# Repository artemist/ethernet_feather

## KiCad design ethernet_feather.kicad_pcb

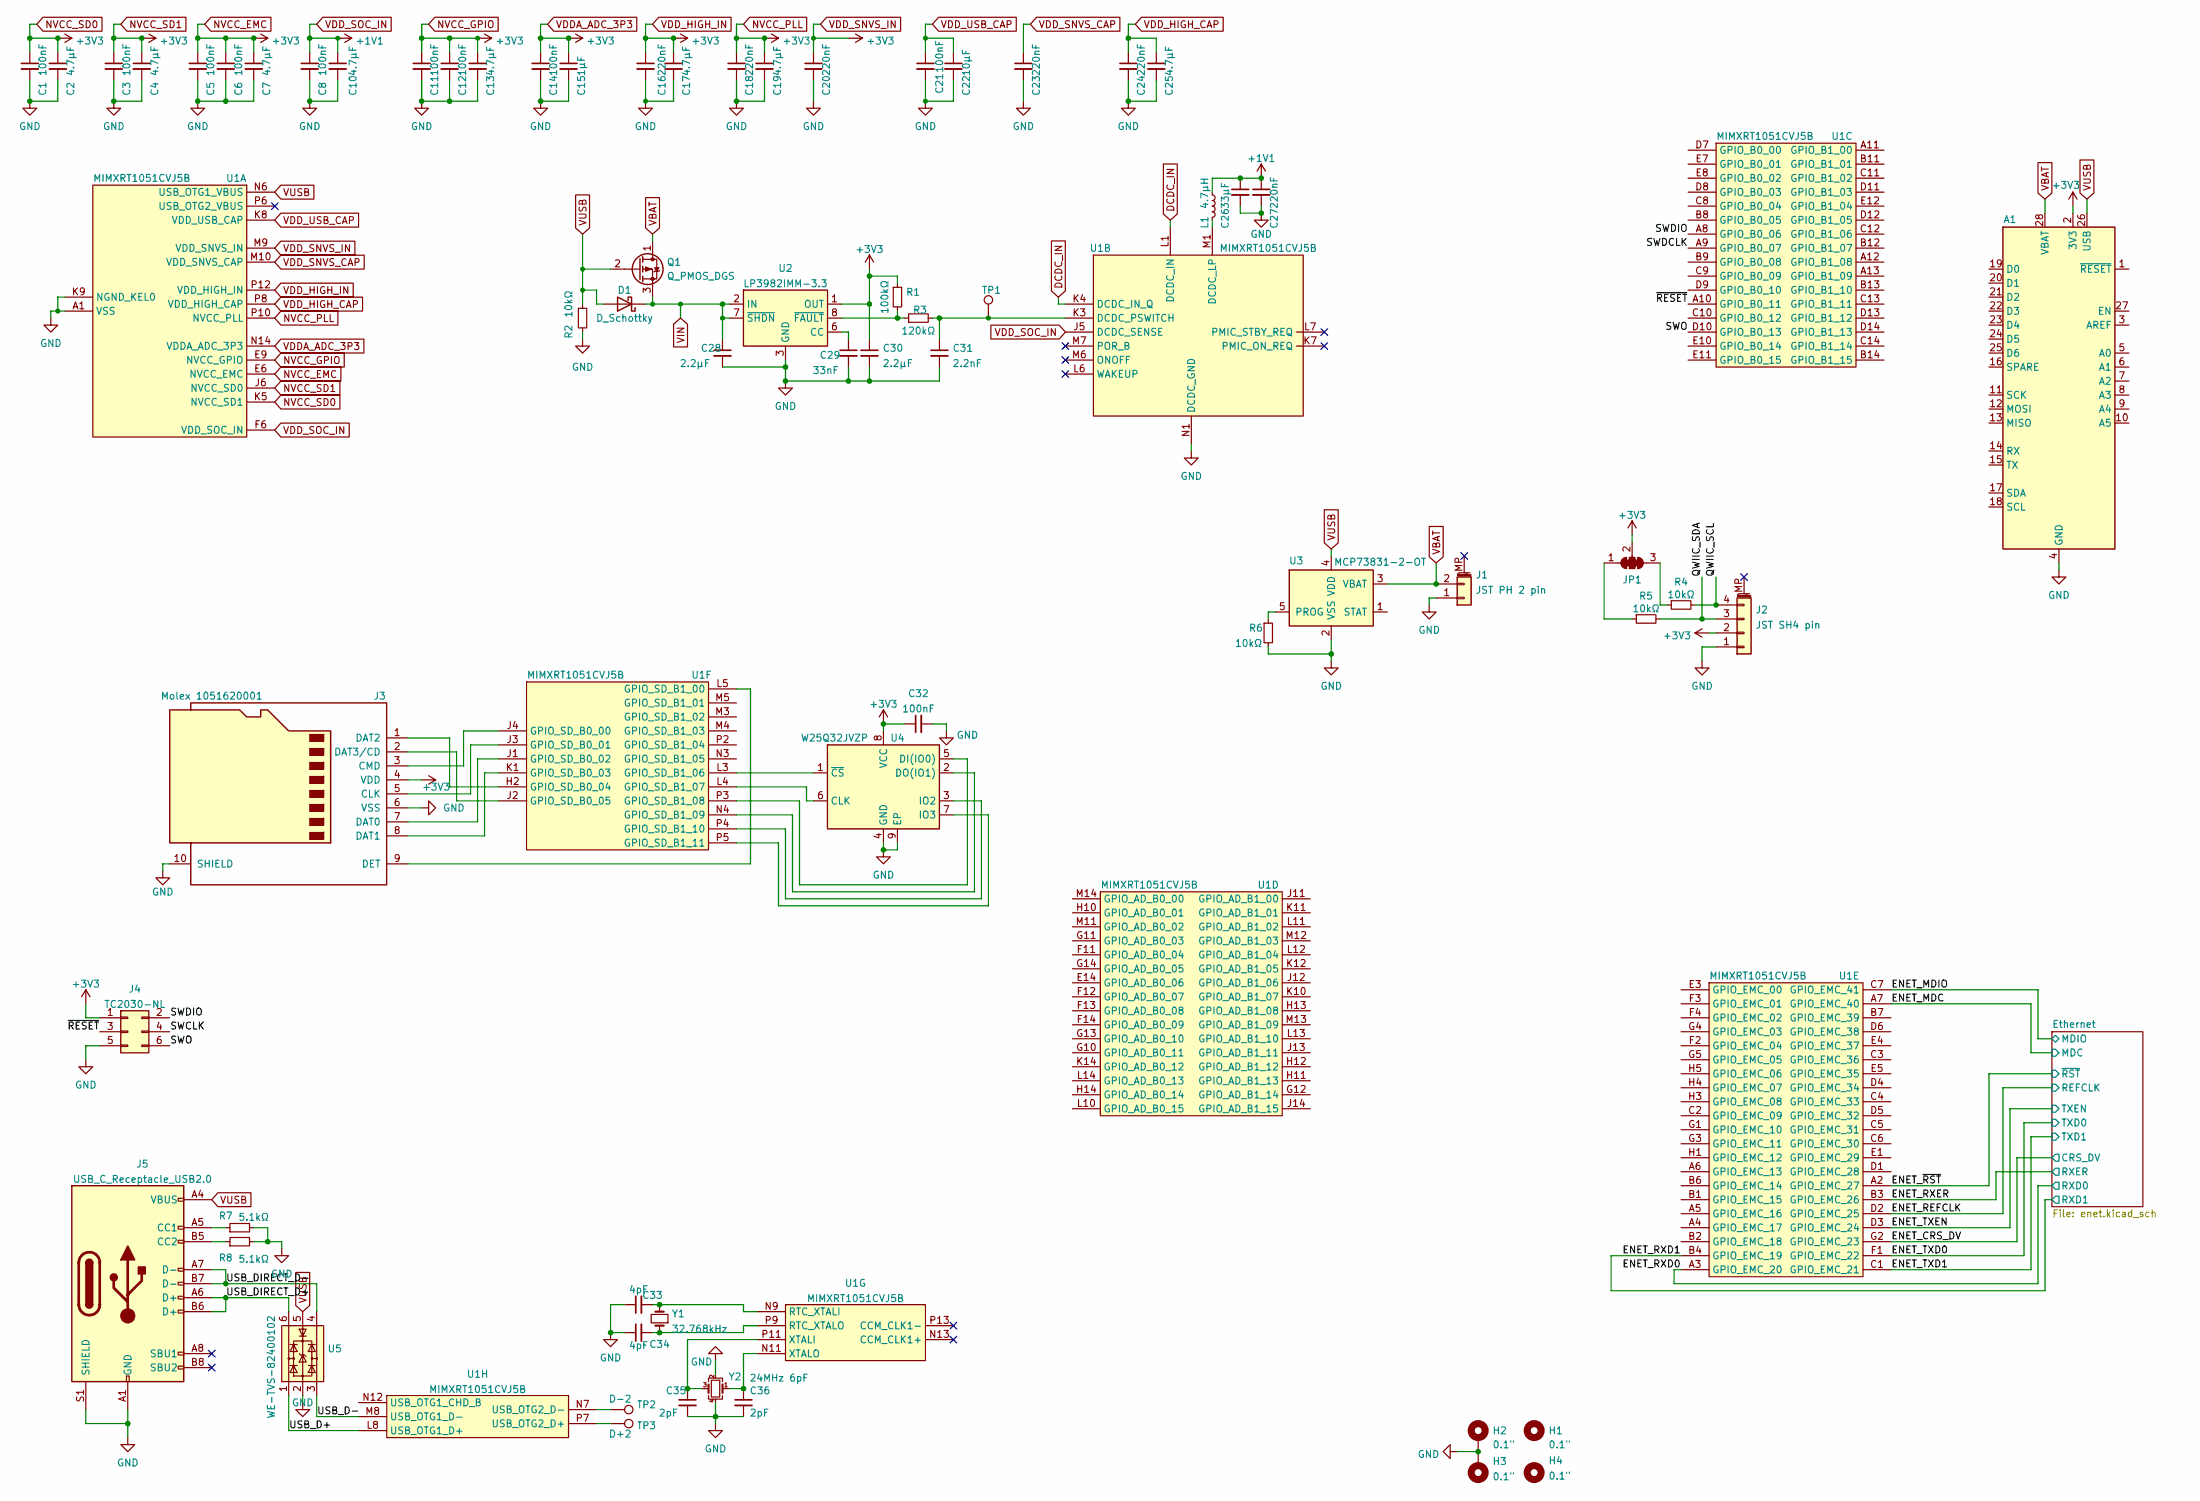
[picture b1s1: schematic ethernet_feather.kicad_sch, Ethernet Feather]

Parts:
A1: Adafruit_Feather_Generic; Adafruit_Feather
C1, C3, C5, C6, C8, C11, C12, C14, C21, C32: 100nF; C_0402_1005Metric
C2, C4, C7, C10, C13, C17, C19, C25: 4.7µF; C_0402_1005Metric
C15: 1µF; C_0402_1005Metric
C16, C18, C20, C23, C24, C27: 220nF; C_0402_1005Metric
C22: 10µF; C_0402_1005Metric
C26: 33µF; C_0402_1005Metric
C28, C30: 2.2µF; C_0402_1005Metric
C29: 33nF; C_0402_1005Metric
C31: 2.2nF; C_0402_1005Metric
C33, C34: 4pF; C_0402_1005Metric
C35, C36: 2pF; C_0402_1005Metric
D1: D_Schottky; D_SOD-323
H1, H4: 0.1"; MountingHole_2.5mm_Small
H2, H3: 0.1"; MountingHole_2.5mm_Pad_Small
J1: JST PH 2 pin; JST_PH_S2B-PH-SM4-TB_1x02-1MP_P2.00mm_Horizontal
J2: JST SH4 pin; JST_SH_SM04B-SRSS-TB_1x04-1MP_P1.00mm_Horizontal
J3: Molex 1051620001; microSD_HC_Molex_1051620001
J4: TC2030-NL; Tag-Connect_TC2030-IDC-NL_2x03_P1.27mm_Vertical
J5: USB_C_Receptacle_USB2.0; USB_C_Receptacle_HRO_TYPE-C-31-M-12
JP1: SolderJumper_3_Bridged123; SolderJumper-3_P1.3mm_Bridged123_RoundedPad1.0x1.5mm
L1: 4.7µH; L_0603_1608Metric
Q1: Q_PMOS_DGS; SOT-23
R1: 100kΩ; R_0402_1005Metric
R2, R4, R5, R6: 10kΩ; R_0402_1005Metric
R3: 120kΩ; R_0402_1005Metric
R7, R8: 5.1kΩ; R_0402_1005Metric
TP1: TestPoint; TestPoint_Pad_D1.0mm
TP2: D-2; TestPoint_Pad_D1.0mm
TP3: D+2; TestPoint_Pad_D1.0mm
U1: MIMXRT1051CVJ5B; LFBGA-196_12x12mm_Layout14x14_P0.8mm
U2: LP3982IMM-3.3; VSSOP-8_3.0x3.0mm_P0.65mm
U3: MCP73831-2-OT; SOT-23-5
U4: W25Q32JVZP; WSON-8-1EP_6x5mm_P1.27mm_EP3.4x4.3mm
U5: WE-TVS-82400102; SOT-23-6
Y1: 32.768kHz; Crystal_SMD_3215-2Pin_3.2x1.5mm
Y2: 24MHz 6pF; Crystal_SMD_2016-4Pin_2.0x1.6mm; Part Number XRCGB24M000F0L00R0

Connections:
/ENET_CRS_DV: U1.G2 (GPIO_EMC_23); also elsewhere on the board
/ENET_MDC: U1.A7 (GPIO_EMC_40); also elsewhere on the board
/ENET_MDIO: U1.C7 (GPIO_EMC_41); also elsewhere on the board
/ENET_REFCLK: U1.D2 (GPIO_EMC_25); also elsewhere on the board
/ENET_RXD0: U1.A3 (GPIO_EMC_20); also elsewhere on the board
/ENET_RXD1: U1.B4 (GPIO_EMC_19); also elsewhere on the board
/ENET_RXER: U1.B3 (GPIO_EMC_26); also elsewhere on the board
/ENET_TXD0: U1.F1 (GPIO_EMC_22); also elsewhere on the board
/ENET_TXD1: U1.C1 (GPIO_EMC_21); also elsewhere on the board
/ENET_TXEN: U1.D3 (GPIO_EMC_24); also elsewhere on the board
/ENET_~RST: U1.A2 (GPIO_EMC_27); also elsewhere on the board
/QWIIC_SCL: J2.4, R4.2
/QWIIC_SDA: J2.3, R5.2
/SWCLK: J4.4
/SWDCLK: U1.A9 (GPIO_B0_07)
/SWDIO: J4.2, U1.A8 (GPIO_B0_06)
/SWO: J4.6, U1.D10 (GPIO_B0_13)
/USB_D+: U1.L8 (USB_OTG1_D+), U5.1
/USB_D-: U1.M8 (USB_OTG1_D-), U5.3
/USB_DIRECT_D+: J5.A6 (D+), J5.B6 (D+), U5.6
/USB_DIRECT_D-: J5.A7 (D-), J5.B7 (D-), U5.4
/~RESET: J4.3, U1.A10 (GPIO_B0_11)
DCDC_GND: A1.4 (GND), C1.2, C2.2, C3.2, C4.2, C5.2, C6.2, C7.2, C8.2, C10.2, C11.2, C12.2, C13.2, C14.2, C15.2, C16.2, C17.2, C18.2, C19.2, C20.2, C21.2, C22.2, C23.2, C24.2, C25.2, C26.2, C27.2, C28.2, C29.2, C30.2, C31.2, C32.2, C33.1, C34.1, C35.2, C36.2, H2.1, H3.1, J1.1, J2.1, J3.6 (VSS), J3.10 (SHIELD), J4.5, J5.A1 (GND), J5.A12 (GND), J5.B1 (GND), J5.B12 (GND), J5.S1 (SHIELD), R2.2, R6.2, R7.2, R8.2, U1.A1 (VSS), U1.A14 (VSS), U1.B5 (VSS), U1.B10 (VSS), U1.E2 (VSS), U1.E13 (VSS), U1.G7 (VSS), U1.G8 (VSS), U1.H7 (VSS), U1.H8 (VSS), U1.J7 (VSS), U1.J8 (VSS), U1.K2 (VSS), U1.K9 (NGND_KEL0), U1.K13 (VSS), U1.L9 (VSS), U1.N1 (DCDC_GND), U1.N2 (DCDC_GND), U1.N5 (VSS), U1.N8 (VSS), U1.P1 (VSS), U1.P14 (VSS), U2.3 (GND), U3.2 (VSS), U4.4 (GND), U4.9 (EP), U5.2, Y2.2, Y2.4; also elsewhere on the board
DCDC_IN: U1.K4 (DCDC_IN_Q), U1.L1 (DCDC_IN), U1.L2 (DCDC_IN)
NVCC_EMC: A1.2 (3V3), C1.1, C2.1, C3.1, C4.1, C5.1, C6.1, C7.1, C11.1, C12.1, C13.1, C14.1, C15.1, C16.1, C17.1, C18.1, C19.1, C20.1, C30.1, C32.1, J2.2, J3.4 (VDD), J4.1, JP1.2 (C), R1.1, U1.E6 (NVCC_EMC), U1.E9 (NVCC_GPIO), U1.F5 (NVCC_EMC), U1.F10 (NVCC_GPIO), U1.J6 (NVCC_SD0), U1.J10 (NVCC_GPIO), U1.K5 (NVCC_SD1), U1.M9 (VDD_SNVS_IN), U1.N14 (VDDA_ADC_3P3), U1.P10 (NVCC_PLL), U1.P12 (VDD_HIGH_IN), U2.1 (OUT), U2.4 (OUT), U4.8 (VCC); also elsewhere on the board
unnamed: C29.1, U2.6 (CC)
unnamed: C31.1, R3.2, TP1.1, U1.K3 (DCDC_PSWITCH)
unnamed: C33.2, U1.N9 (RTC_XTALI), Y1.2
unnamed: C34.2, U1.P9 (RTC_XTALO), Y1.1
unnamed: C35.1, U1.P11 (XTALI), Y2.3
unnamed: C36.1, U1.N11 (XTALO), Y2.1
unnamed: J3.1 (DAT2), U1.H2 (GPIO_SD_B0_04)
unnamed: J3.2 (DAT3/CD), U1.J2 (GPIO_SD_B0_05)
unnamed: J3.3 (CMD), U1.J4 (GPIO_SD_B0_00)
unnamed: J3.5 (CLK), U1.J3 (GPIO_SD_B0_01)
unnamed: J3.7 (DAT0), U1.J1 (GPIO_SD_B0_02)
unnamed: J3.8 (DAT1), U1.K1 (GPIO_SD_B0_03)
unnamed: J3.9 (DET), U1.L5 (GPIO_SD_B1_00)
unnamed: J5.A5 (CC1), R7.1
unnamed: J5.B5 (CC2), R8.1
unnamed: JP1.1 (A), R5.1
unnamed: JP1.3 (B), R4.1
unnamed: L1.2, U1.M1 (DCDC_LP), U1.M2 (DCDC_LP)
unnamed: R1.2, R3.1, U2.8 (~FAULT)
unnamed: R6.1, U3.5 (PROG)
unnamed: TP2.1, U1.N7 (USB_OTG2_D-)
unnamed: TP3.1, U1.P7 (USB_OTG2_D+)
unnamed: U1.L3 (GPIO_SD_B1_06), U4.1 (~CS)
unnamed: U1.L4 (GPIO_SD_B1_07), U4.6 (CLK)
unnamed: U1.N4 (GPIO_SD_B1_09), U4.2 (DO(IO1))
unnamed: U1.P3 (GPIO_SD_B1_08), U4.5 (DI(IO0))
unnamed: U1.P4 (GPIO_SD_B1_10), U4.3 (IO2)
unnamed: U1.P5 (GPIO_SD_B1_11), U4.7 (IO3)
VBAT: A1.28 (VBAT), J1.2, Q1.1 (D), U3.3 (VBAT)
VDD_HIGH_CAP: C24.1, C25.1, U1.P8 (VDD_HIGH_CAP)
VDD_SNVS_CAP: C23.1, U1.M10 (VDD_SNVS_CAP)
VDD_SOC_IN: C8.1, C10.1, C26.1, C27.1, L1.1, U1.F6 (VDD_SOC_IN), U1.F7 (VDD_SOC_IN), U1.F8 (VDD_SOC_IN), U1.F9 (VDD_SOC_IN), U1.G6 (VDD_SOC_IN), U1.G9 (VDD_SOC_IN), U1.H6 (VDD_SOC_IN), U1.H9 (VDD_SOC_IN), U1.J5 (DCDC_SENSE), U1.J9 (VDD_SOC_IN); also elsewhere on the board
VDD_USB_CAP: C21.1, C22.1, U1.K8 (VDD_USB_CAP)
VIN: C28.1, D1.1 (K), Q1.3 (S), U2.2 (IN), U2.7 (~SHDN)
VUSB: A1.26 (USB), D1.2 (A), J5.A4 (VBUS), J5.A9 (VBUS), J5.B4 (VBUS), J5.B9 (VBUS), Q1.2 (G), R2.1, U1.N6 (USB_OTG1_VBUS), U3.4 (VDD), U5.5

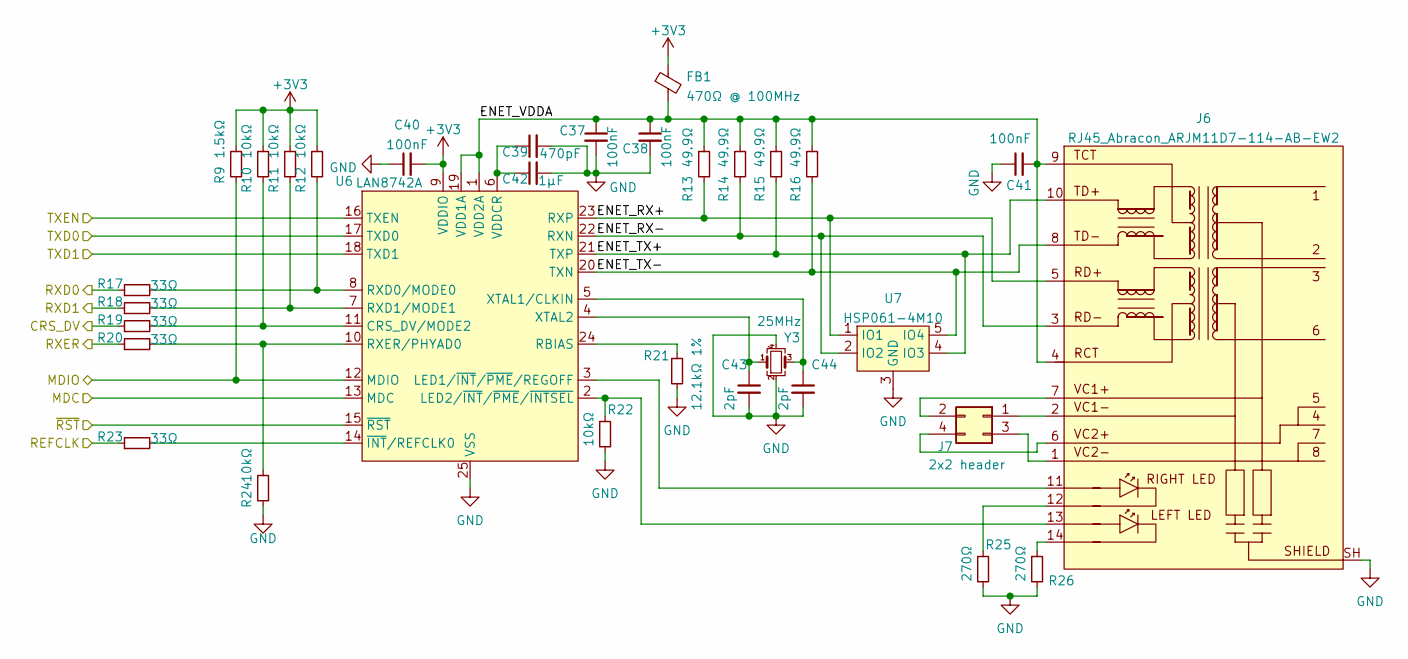
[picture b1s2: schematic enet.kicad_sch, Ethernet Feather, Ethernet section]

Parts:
C37, C38, C40, C41: 100nF; C_0402_1005Metric
C39: 470pF; C_0402_1005Metric
C42: 1µF; C_0402_1005Metric
C43, C44: 2pF; C_0402_1005Metric
FB1: 470Ω @ 100MHz; L_0603_1608Metric
J6: RJ45_Abracon_ARJM11D7-114-AB-EW2; RJ45_Abracon_ARJM11D7-114
J7: 2x2 header; PinSocket_2x02_P2.54mm_Vertical
R9: 1.5kΩ; R_0402_1005Metric
R10, R11, R12, R22, R24: 10kΩ; R_0402_1005Metric
R13, R14, R15, R16: 49.9Ω; R_0402_1005Metric
R17, R18, R19, R20, R23: 33Ω; R_0402_1005Metric
R21: 12.1kΩ 1%; R_0402_1005Metric
R25, R26: 270Ω; R_0402_1005Metric
U6: LAN8742A; VQFN-24-1EP_4x4mm_P0.5mm_EP2.45x2.45mm_ThermalVias
U7: HSP061-4M10; ST_µQFN-10L
Y3: 25MHz; Crystal_SMD_2016-4Pin_2.0x1.6mm

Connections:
/ENET_CRS_DV: R19.1; also elsewhere on the board
/ENET_MDC: U6.13 (MDC); also elsewhere on the board
/ENET_MDIO: R9.2, U6.12 (MDIO); also elsewhere on the board
/ENET_REFCLK: R23.1; also elsewhere on the board
/ENET_RXD0: R17.1; also elsewhere on the board
/ENET_RXD1: R18.1; also elsewhere on the board
/ENET_RXER: R20.1; also elsewhere on the board
/ENET_TXD0: U6.17 (TXD0); also elsewhere on the board
/ENET_TXD1: U6.18 (TXD1); also elsewhere on the board
/ENET_TXEN: U6.16 (TXEN); also elsewhere on the board
/ENET_~RST: U6.15 (~RST); also elsewhere on the board
/Ethernet/ENET_RX+: J6.5 (CT), R13.2, U6.23 (RXP), U7.1 (IO1), U7.10 (NC)
/Ethernet/ENET_RX-: J6.3 (RD+), R14.2, U6.22 (RXN), U7.2 (IO2), U7.9 (NC)
/Ethernet/ENET_TX+: J6.10 (TD+), R15.2, U6.21 (TXP), U7.4 (IO3), U7.7 (NC)
/Ethernet/ENET_TX-: J6.8 (TD-), R16.2, U6.20 (TXN), U7.5 (IO4), U7.6 (NC)
/Ethernet/ENET_VDDA: C37.1, C38.1, C41.2, FB1.2, J6.4 (CT), J6.9 (V+), R13.1, R14.1, R15.1, R16.1, U6.1 (VDD2A), U6.19 (VDD1A)
DCDC_GND: C37.2, C38.2, C39.2, C40.1, C41.1, C42.2, C43.2, C44.2, J6.SH (SHIELD), R21.2, R22.2, R24.2, R25.2, R26.2, U6.25 (VSS), U7.3 (GND), U7.8 (GND), Y3.2, Y3.4; also elsewhere on the board
NVCC_EMC: C40.2, FB1.1, R9.1, R10.1, R11.1, R12.1, U6.9 (VDDIO); also elsewhere on the board
unnamed: C39.1, C42.1, U6.6 (VDDCR)
unnamed: C43.1, U6.4 (XTAL2), Y3.1
unnamed: C44.1, U6.5 (XTAL1/CLKIN), Y3.3
unnamed: J6.1 (TD+), J7.3
unnamed: J6.2 (TD-), J7.1
unnamed: J6.6 (RD-), J7.4
unnamed: J6.7, J7.2
unnamed: J6.11 (RLED+), U6.3 (LED1/~INT/~PME/REGOFF)
unnamed: J6.12 (RLED-), R25.1
unnamed: J6.13 (LLED+), R22.1, U6.2 (LED2/~INT/~PME/~INTSEL)
unnamed: J6.14 (LLED-), R26.1
unnamed: R10.2, R19.2, U6.11 (CRS_DV/MODE2)
unnamed: R11.2, R18.2, U6.7 (RXD1/MODE1)
unnamed: R12.2, R17.2, U6.8 (RXD0/MODE0)
unnamed: R20.2, R24.1, U6.10 (RXER/PHYAD0)
unnamed: R21.1, U6.24 (RBIAS)
unnamed: R23.2, U6.14 (~INT/REFCLK0)

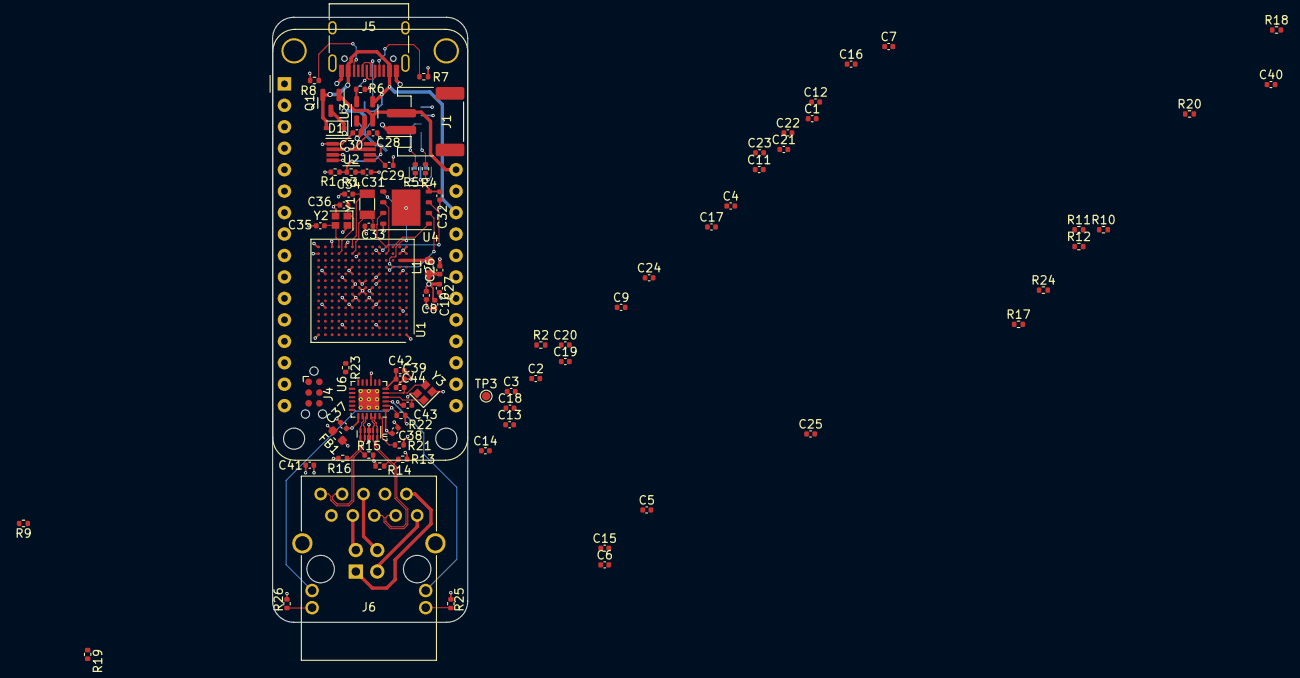
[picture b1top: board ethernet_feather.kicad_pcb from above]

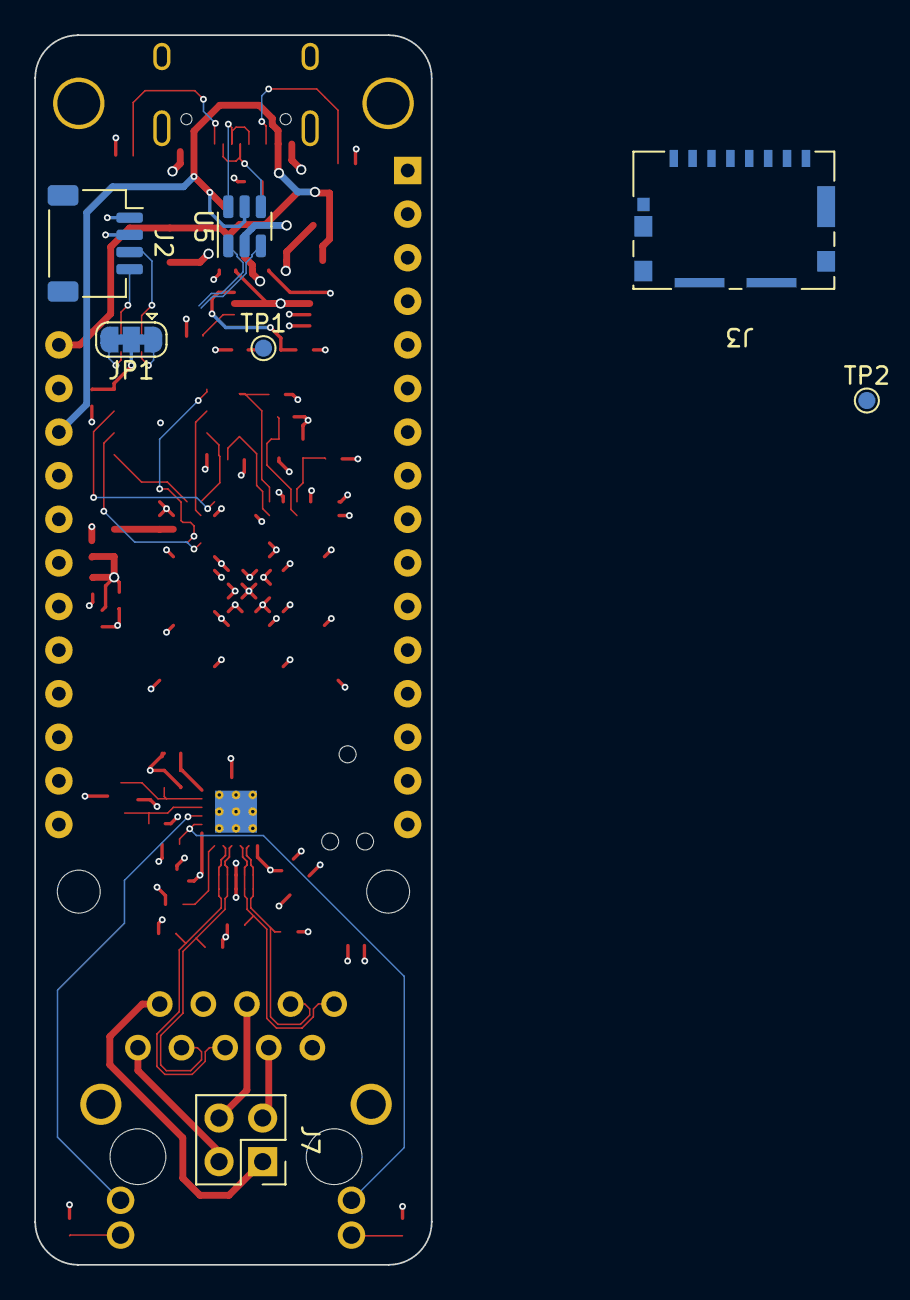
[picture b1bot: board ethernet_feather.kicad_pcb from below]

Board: 4 copper layers, 23.1 x 71.6 mm, 100 parts (7 on the bottom side), 80 nets.

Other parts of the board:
C9: 100nF; C_0402_1005Metric

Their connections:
DCDC_GND: C9.2; also elsewhere on the board
VDD_SOC_IN: C9.1; also elsewhere on the board

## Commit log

2021-10-25 Initial design with SAME70J19B
2021-10-26 Create unmanagably large MIMXRT1052DVJ5B symbol
2021-10-26 Split up MIMXRT1052DVJ5B symbol
2021-10-26 Clean up MIMXRT1052CVJ5B symbol
2021-10-27 Reduce size of symbol
2021-10-27 Add crystals
2021-10-30 Add new Ethernet symbol and Ethernet and BGA footprints
2021-11-02 Most of the HV side captured
2021-11-07 Assign footprints and add LDO
2021-11-09 Add some connectors
2021-11-09 Set basic PCB configuration
2021-11-09 Add LAN8700 symbol
2021-11-09 Remove LAN8700 symbol since it's NRND
2021-11-09 Add LAN8742A symbol
2021-11-09 Add ST HSP061-4M10 symbol and footprint (µQFN-10L)
2021-11-10 Finish PHY schematic (except capacitor values and component selection)
2021-11-10 Select crystals and resonance capacitors
2021-11-11 Split out ethernet schematic
2021-11-18 Some PSU changes, add new solder jumper symbol
2021-12-08 Add microSD card and annotate mostly complete schematic
2021-12-11 YOU CAN'T CUT BACK ON DECOUPLING CAPACITORS! YOU WILL REGRET THIS!
2021-12-11 Start PCB
2021-12-11 Fix up mounting holes, route more flash and microSD
2022-07-04 Old work, I have no idea what this is
